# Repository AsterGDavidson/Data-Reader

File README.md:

# Data-Reader
Items: Teensy 4.1, 10k potentiometer

5V into potentiometer, output pin of potentiometer to pin 14 (A0), remaining pin to ground.

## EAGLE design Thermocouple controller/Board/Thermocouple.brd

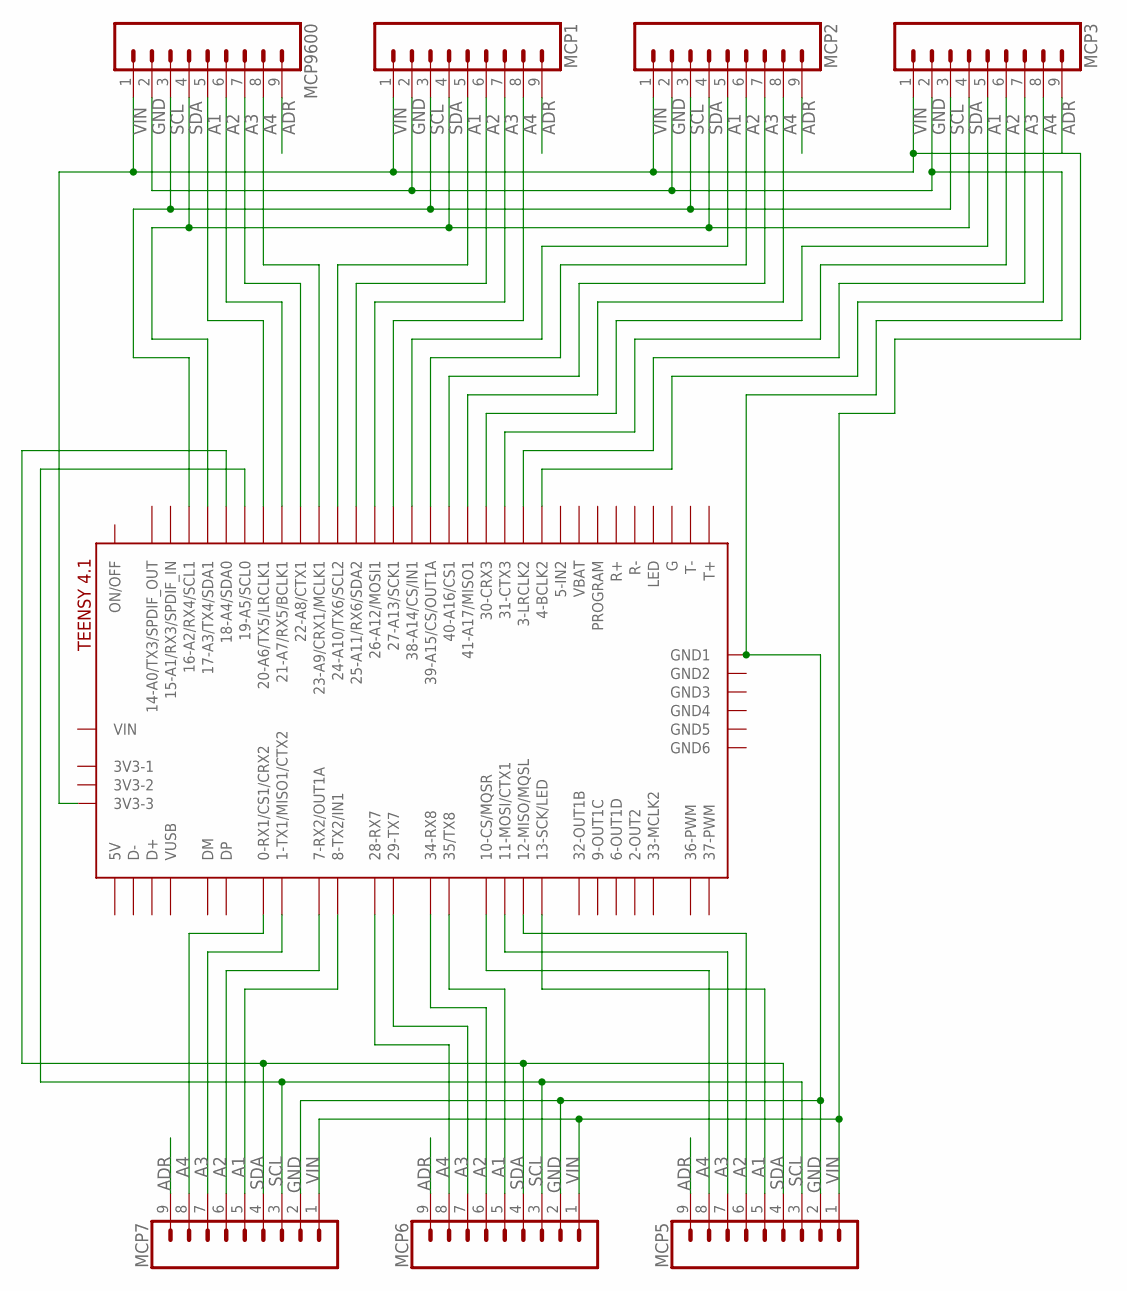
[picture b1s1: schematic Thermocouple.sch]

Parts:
MCP1, MCP2, MCP3, MCP5, MCP6, MCP7, MCP9600: CONN_09; 1X09
U$1: TEENSY41

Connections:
A1: MCP1.5, MCP2.5, MCP3.5, MCP9600.5, U$1.20-A6/TX5/LRCLK1, U$1.24-A10/TX6/SCL2, U$1.30-CRX3, U$1.38-A14/CS/IN1
A2: MCP1.6, MCP2.6, MCP3.6, MCP9600.6, U$1.21-A7/RX5/BCLK1, U$1.25-A11/RX6/SDA2, U$1.31-CTX3, U$1.39-A15/CS/OUT1A
A3: MCP1.7, MCP2.7, MCP3.7, MCP9600.7, U$1.3-LRCLK2, U$1.22-A8/CTX1, U$1.26-A12/MOSI1, U$1.40-A16/CS1
A4: MCP1.8, MCP2.8, MCP3.8, MCP9600.8, U$1.4-BCLK2, U$1.23-A9/CRX1/MCLK1, U$1.27-A13/SCK1, U$1.41-A17/MISO1
ADR: MCP1.9, MCP2.9, MCP3.9, MCP5.9, MCP6.9, MCP7.9, MCP9600.9
GND: MCP1.2, MCP2.2, MCP3.2, MCP5.2, MCP6.2, MCP7.2, MCP9600.2, U$1.GND1
unnamed: MCP7.8, U$1.0-RX1/CS1/CRX2
unnamed: MCP7.7, U$1.1-TX1/MISO1/CTX2
unnamed: MCP7.6, U$1.7-RX2/OUT1A
unnamed: MCP7.5, U$1.8-TX2/IN2 (8-TX2/IN1)
unnamed: MCP6.8, U$1.28-RX7
unnamed: MCP6.7, U$1.29-TX7
unnamed: MCP6.6, U$1.34-RX8
unnamed: MCP6.5, U$1.35-TX8 (35/TX8)
unnamed: MCP5.8, U$1.10-CS\MQSR (10-CS/MQSR)
unnamed: MCP5.7, U$1.11-MOSI/CTX1
unnamed: MCP5.6, U$1.12-MISO/MQSL
unnamed: MCP5.5, U$1.13-SCK/LED
SCL: MCP1.3, MCP2.3, MCP3.3, MCP5.3, MCP6.3, MCP7.3, MCP9600.3, U$1.16-A2/RX4/SCL1, U$1.19-A5/SCL0
SDA: MCP1.4, MCP2.4, MCP3.4, MCP5.4, MCP6.4, MCP7.4, MCP9600.4, U$1.17-A3/TX4/SDA1, U$1.18-A4/SDA0
VIN: MCP1.1, MCP2.1, MCP3.1, MCP5.1, MCP6.1, MCP7.1, MCP9600.1, U$1.3V3-3

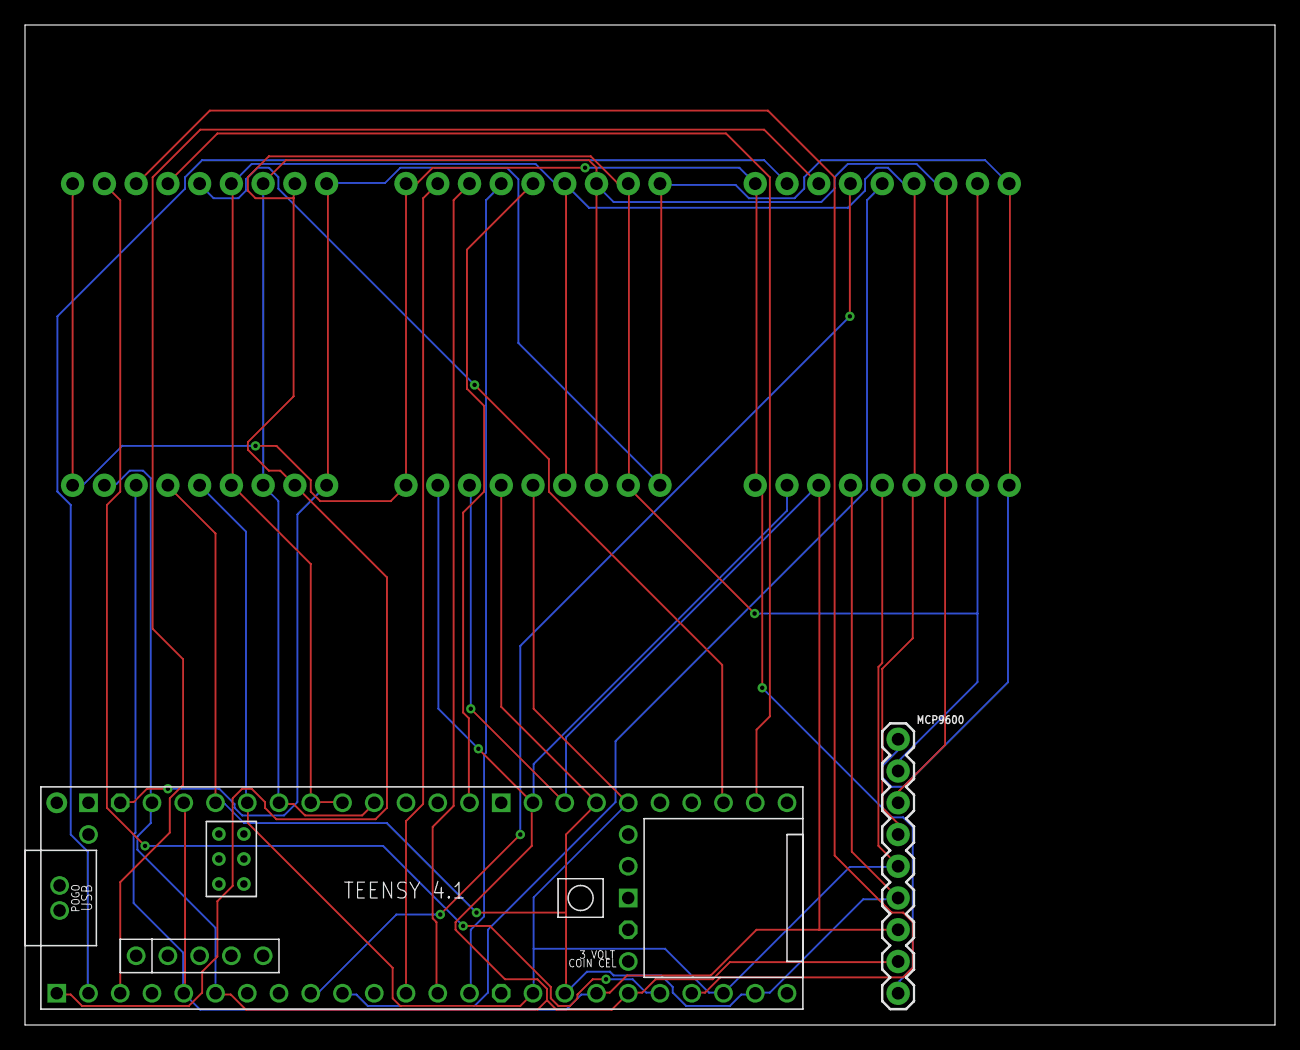
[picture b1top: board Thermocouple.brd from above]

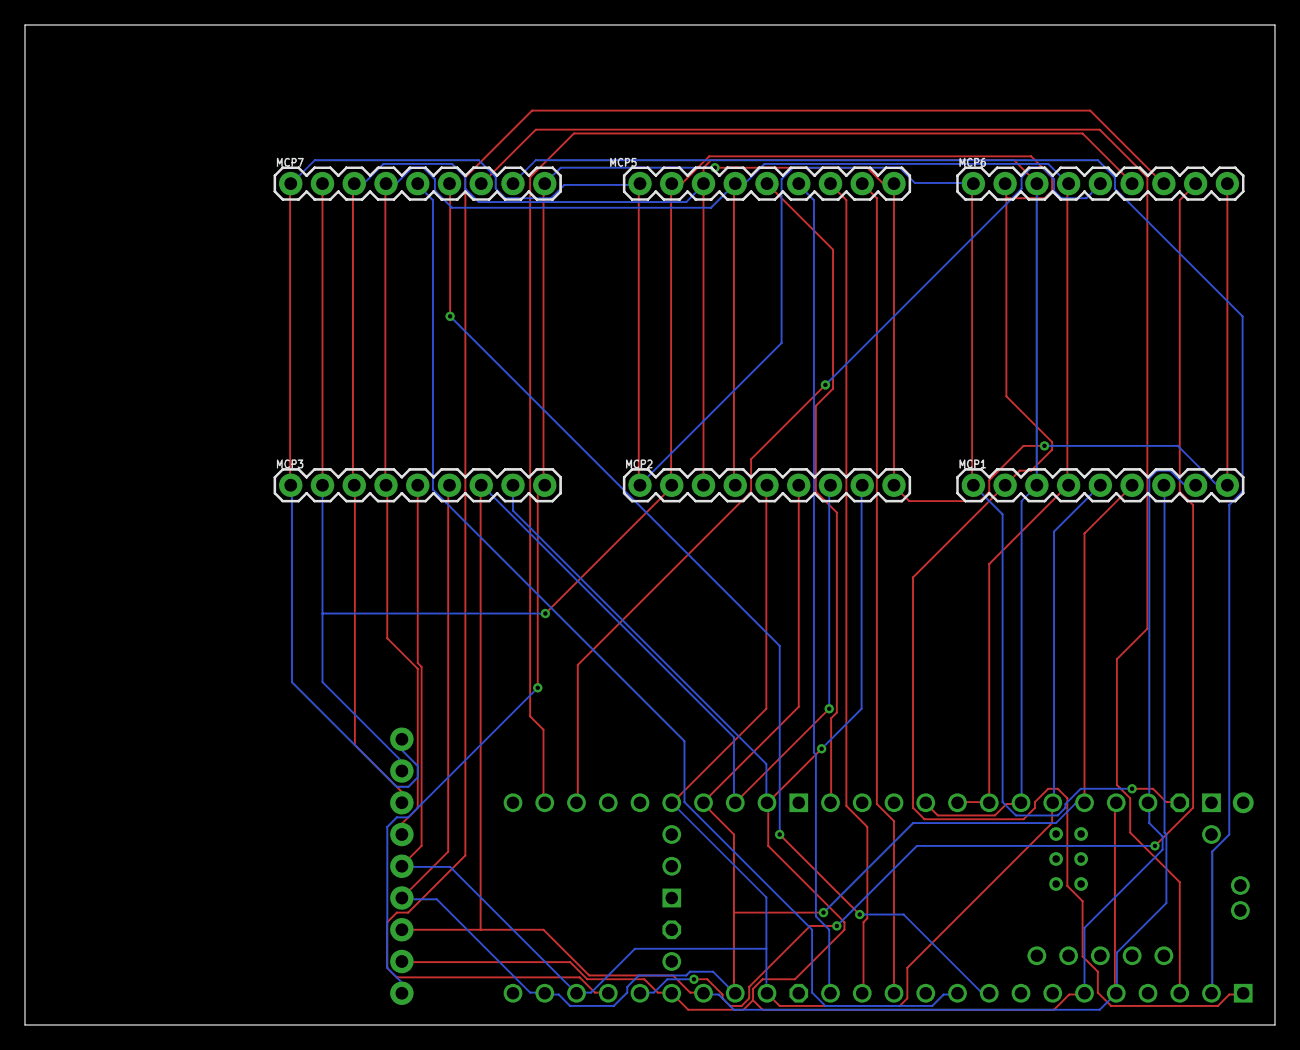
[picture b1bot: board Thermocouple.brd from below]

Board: 2 copper layers, 100.0 x 80.0 mm, 8 parts (6 on the bottom side), 21 nets.

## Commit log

2025-06-17 Rename Setup.md to README.md
2025-06-18 Create huh
2025-06-18 Rename Three_Pots_Read.py to Five_Pots_Read.py
2025-06-18 Rename Three_Pots_Retrieval.cpp to Five_Pots_Retrieval.cpp
2025-06-19 Create AH
2025-06-19 Create Board

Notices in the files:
parts and their libraries:
SparkFun-Connectors: Licensing: Creative Commons ShareAlike 4.0 International - https://creativecommons.org/licenses/by-sa/4.0
